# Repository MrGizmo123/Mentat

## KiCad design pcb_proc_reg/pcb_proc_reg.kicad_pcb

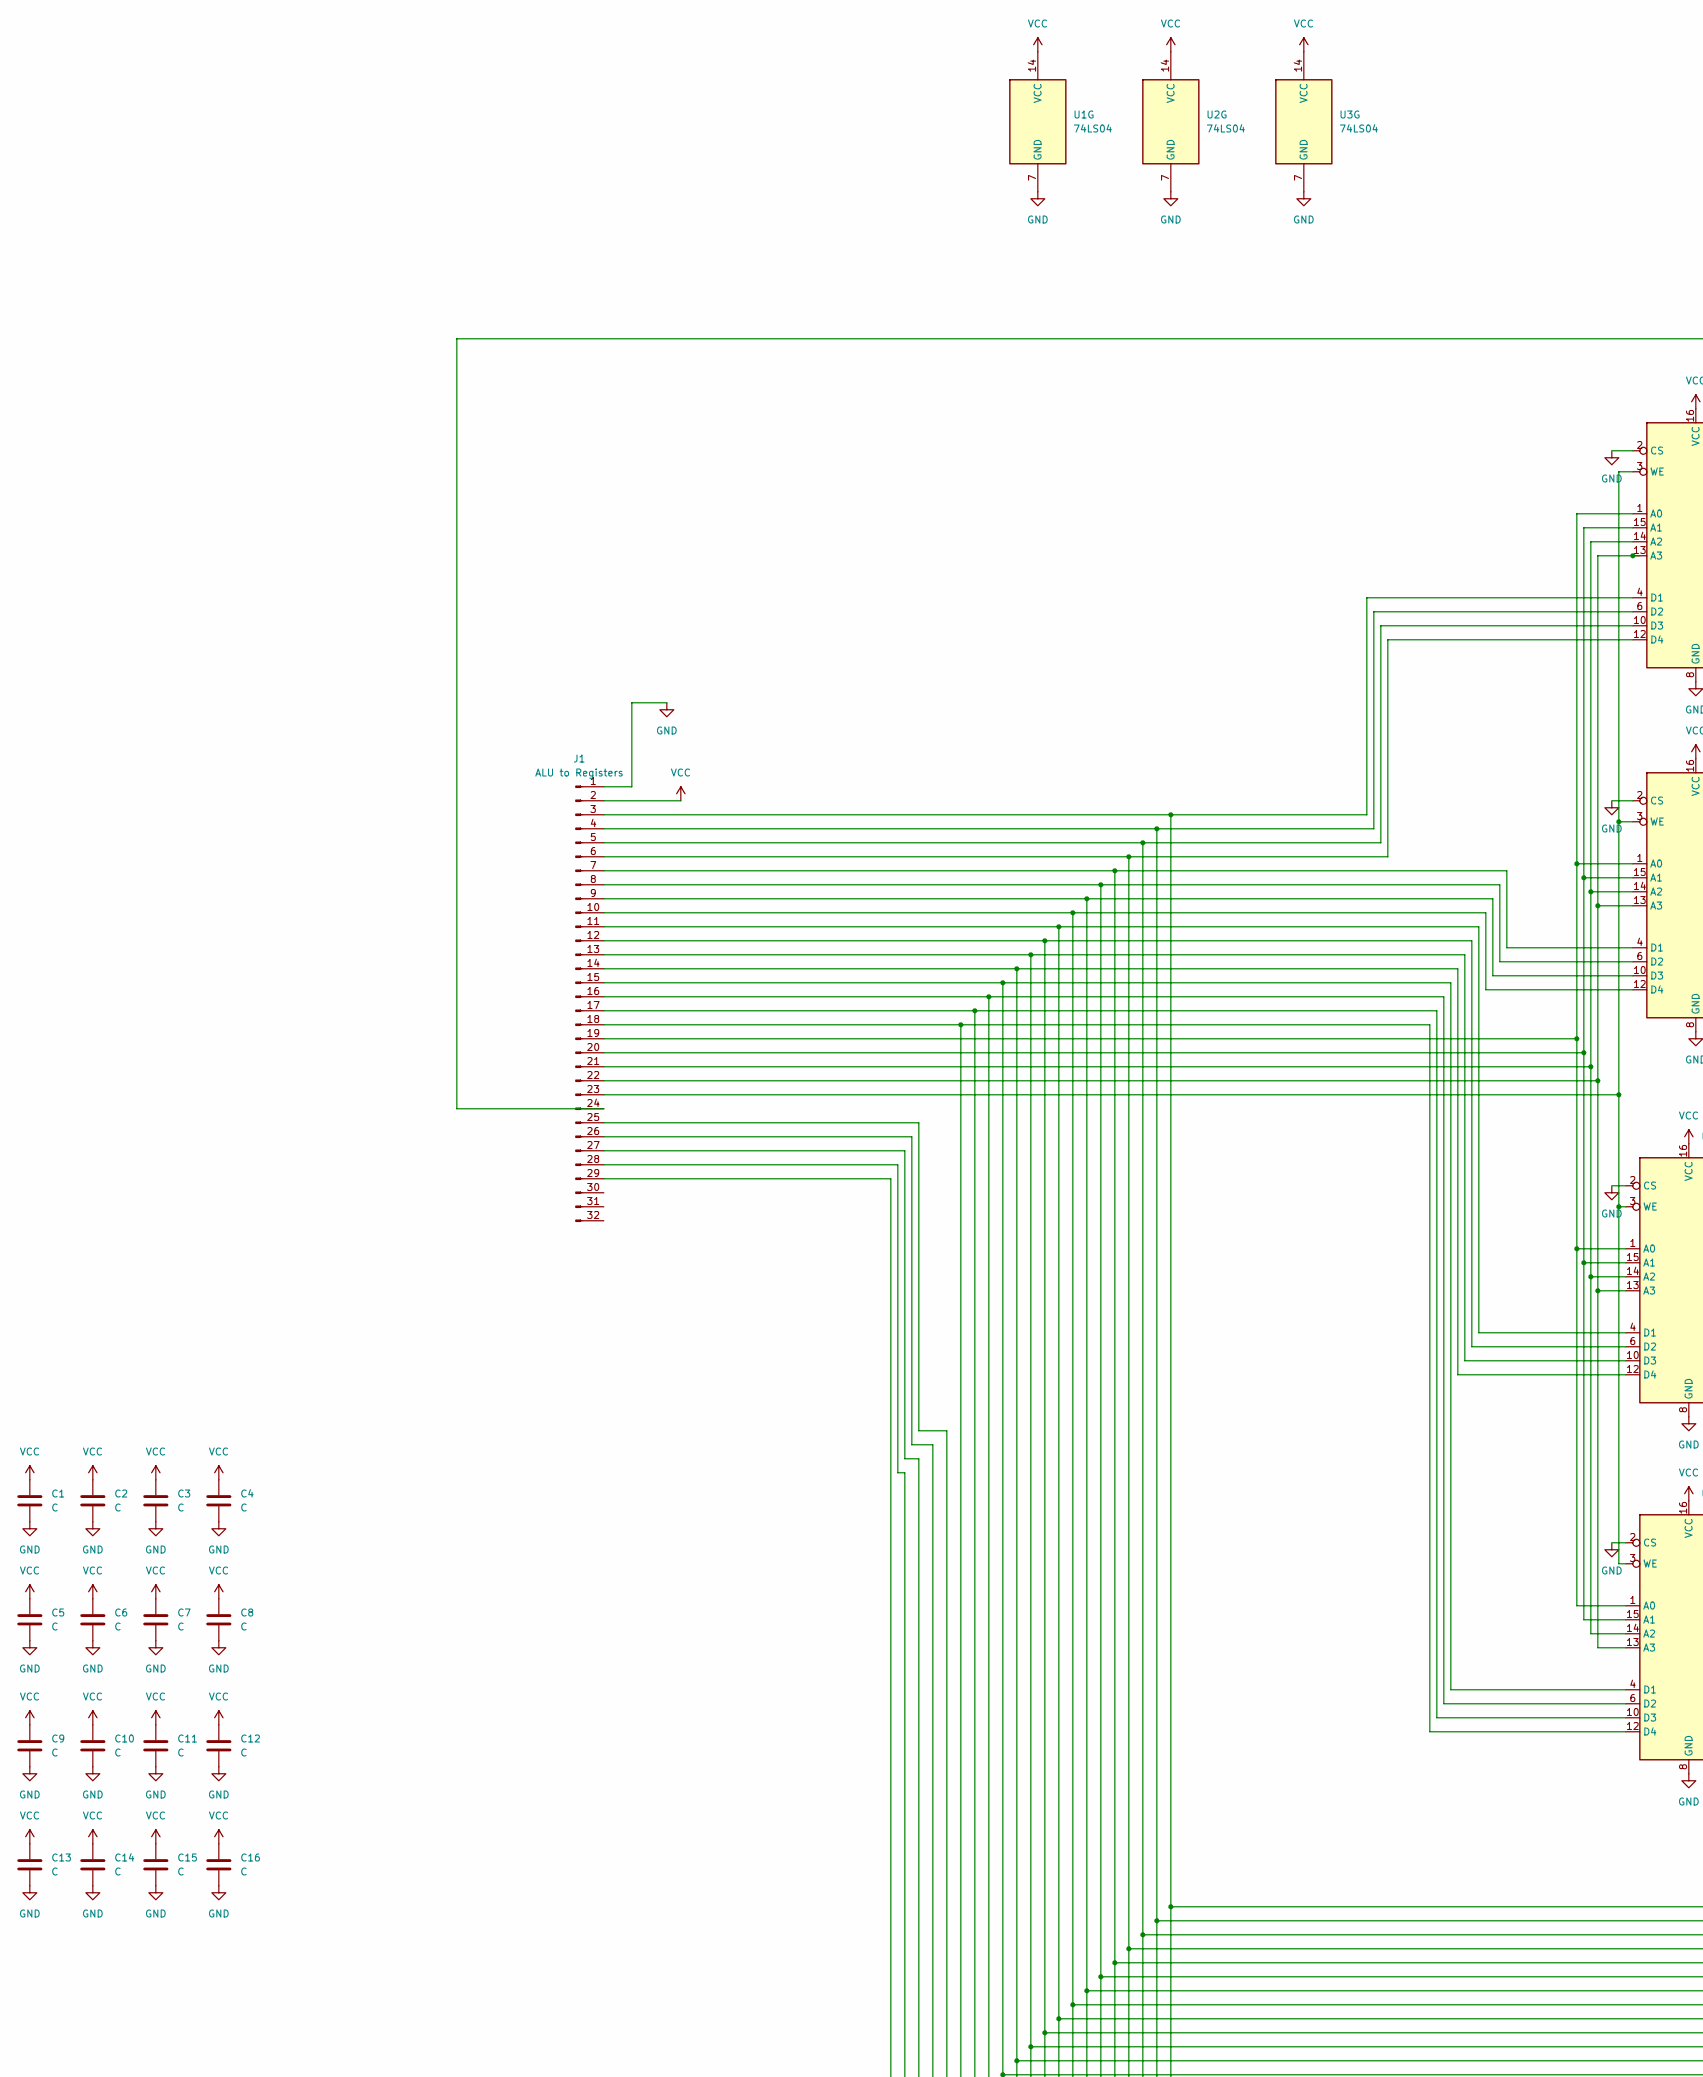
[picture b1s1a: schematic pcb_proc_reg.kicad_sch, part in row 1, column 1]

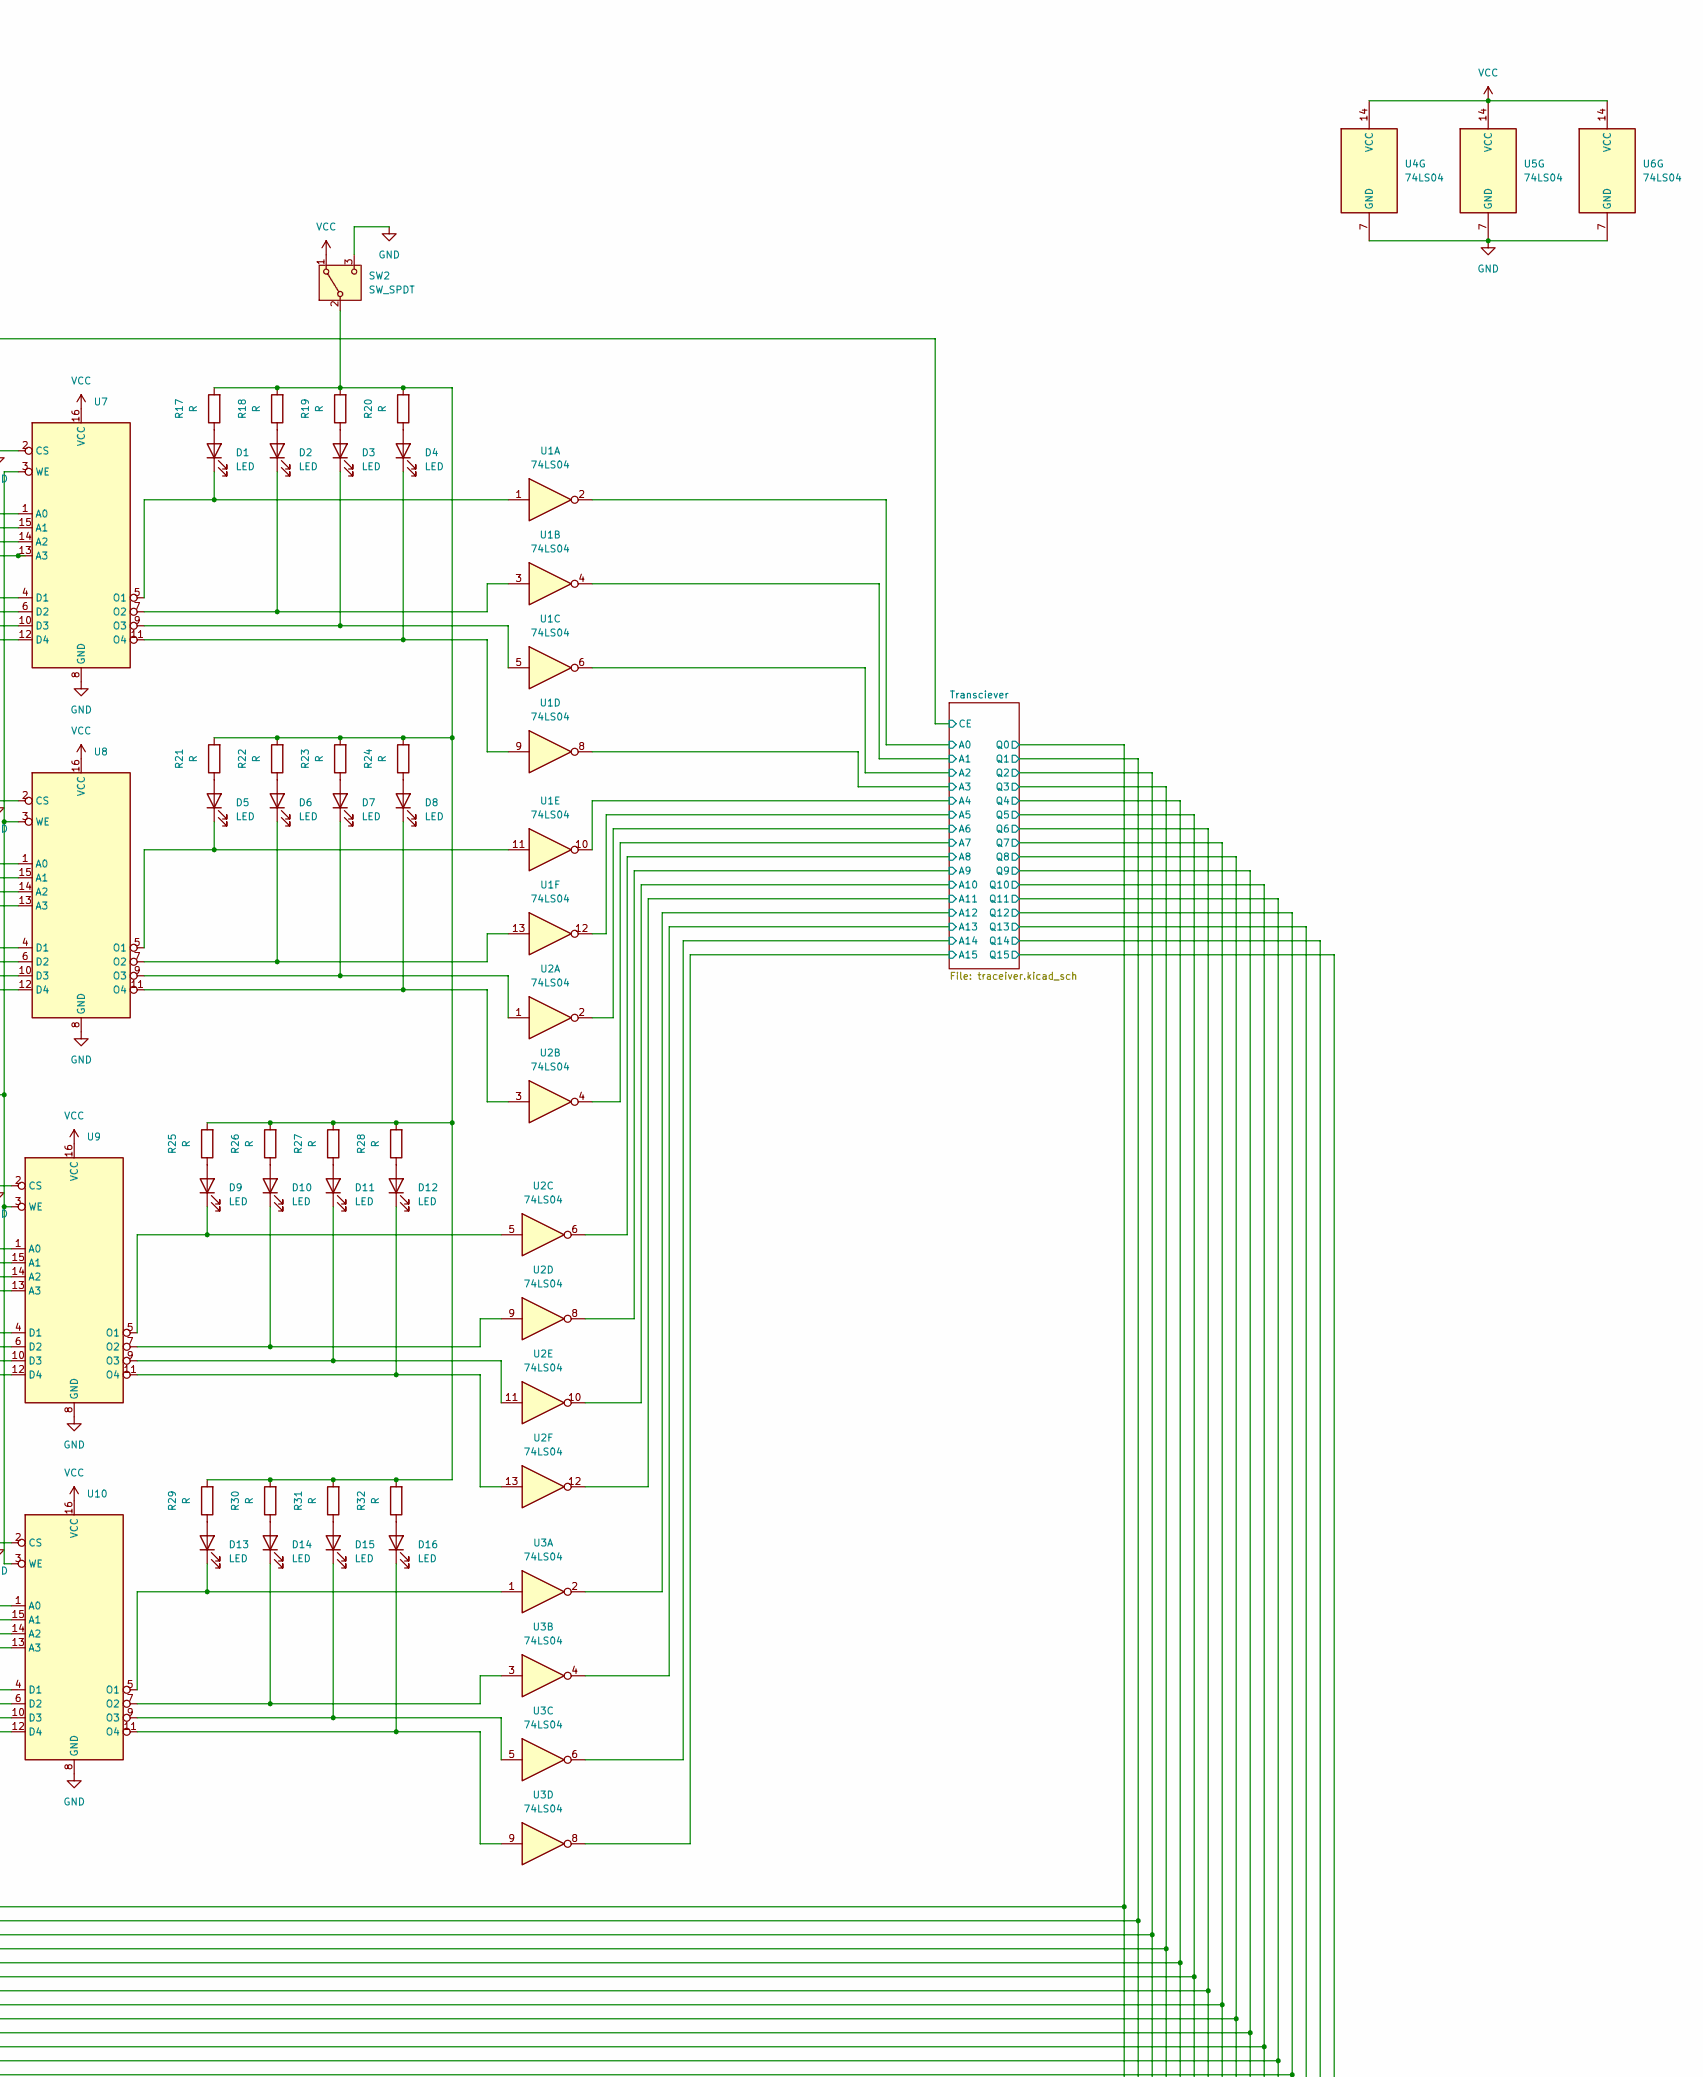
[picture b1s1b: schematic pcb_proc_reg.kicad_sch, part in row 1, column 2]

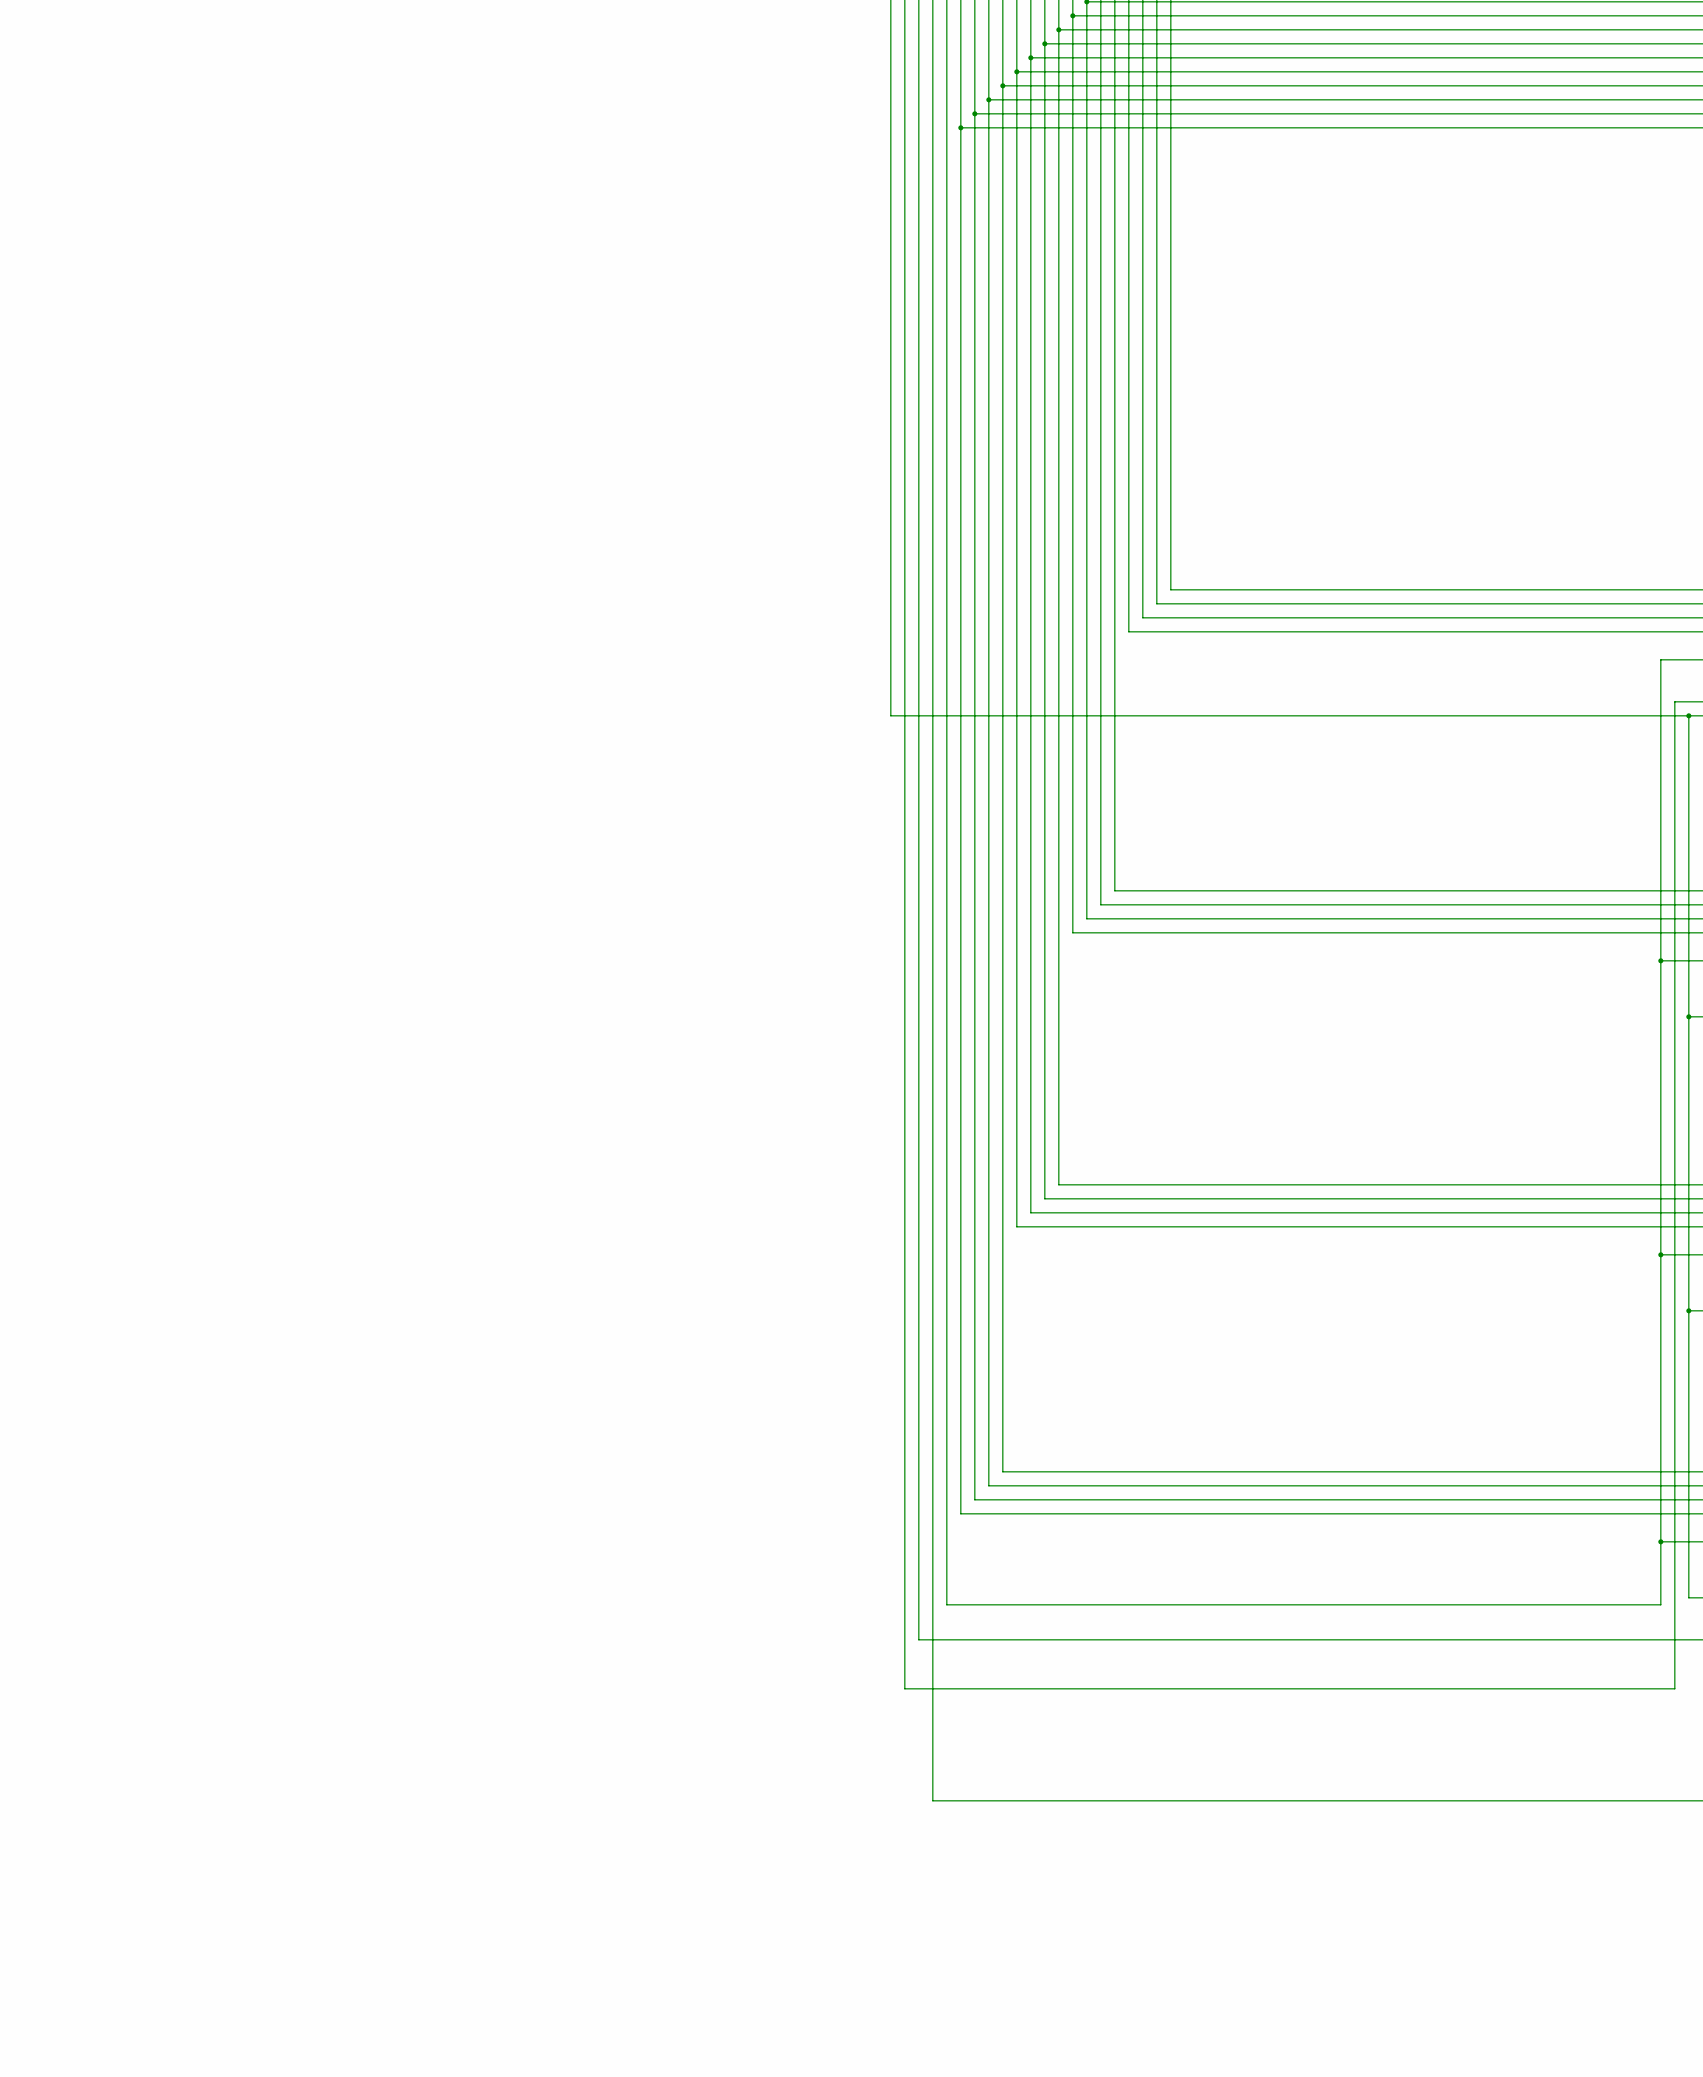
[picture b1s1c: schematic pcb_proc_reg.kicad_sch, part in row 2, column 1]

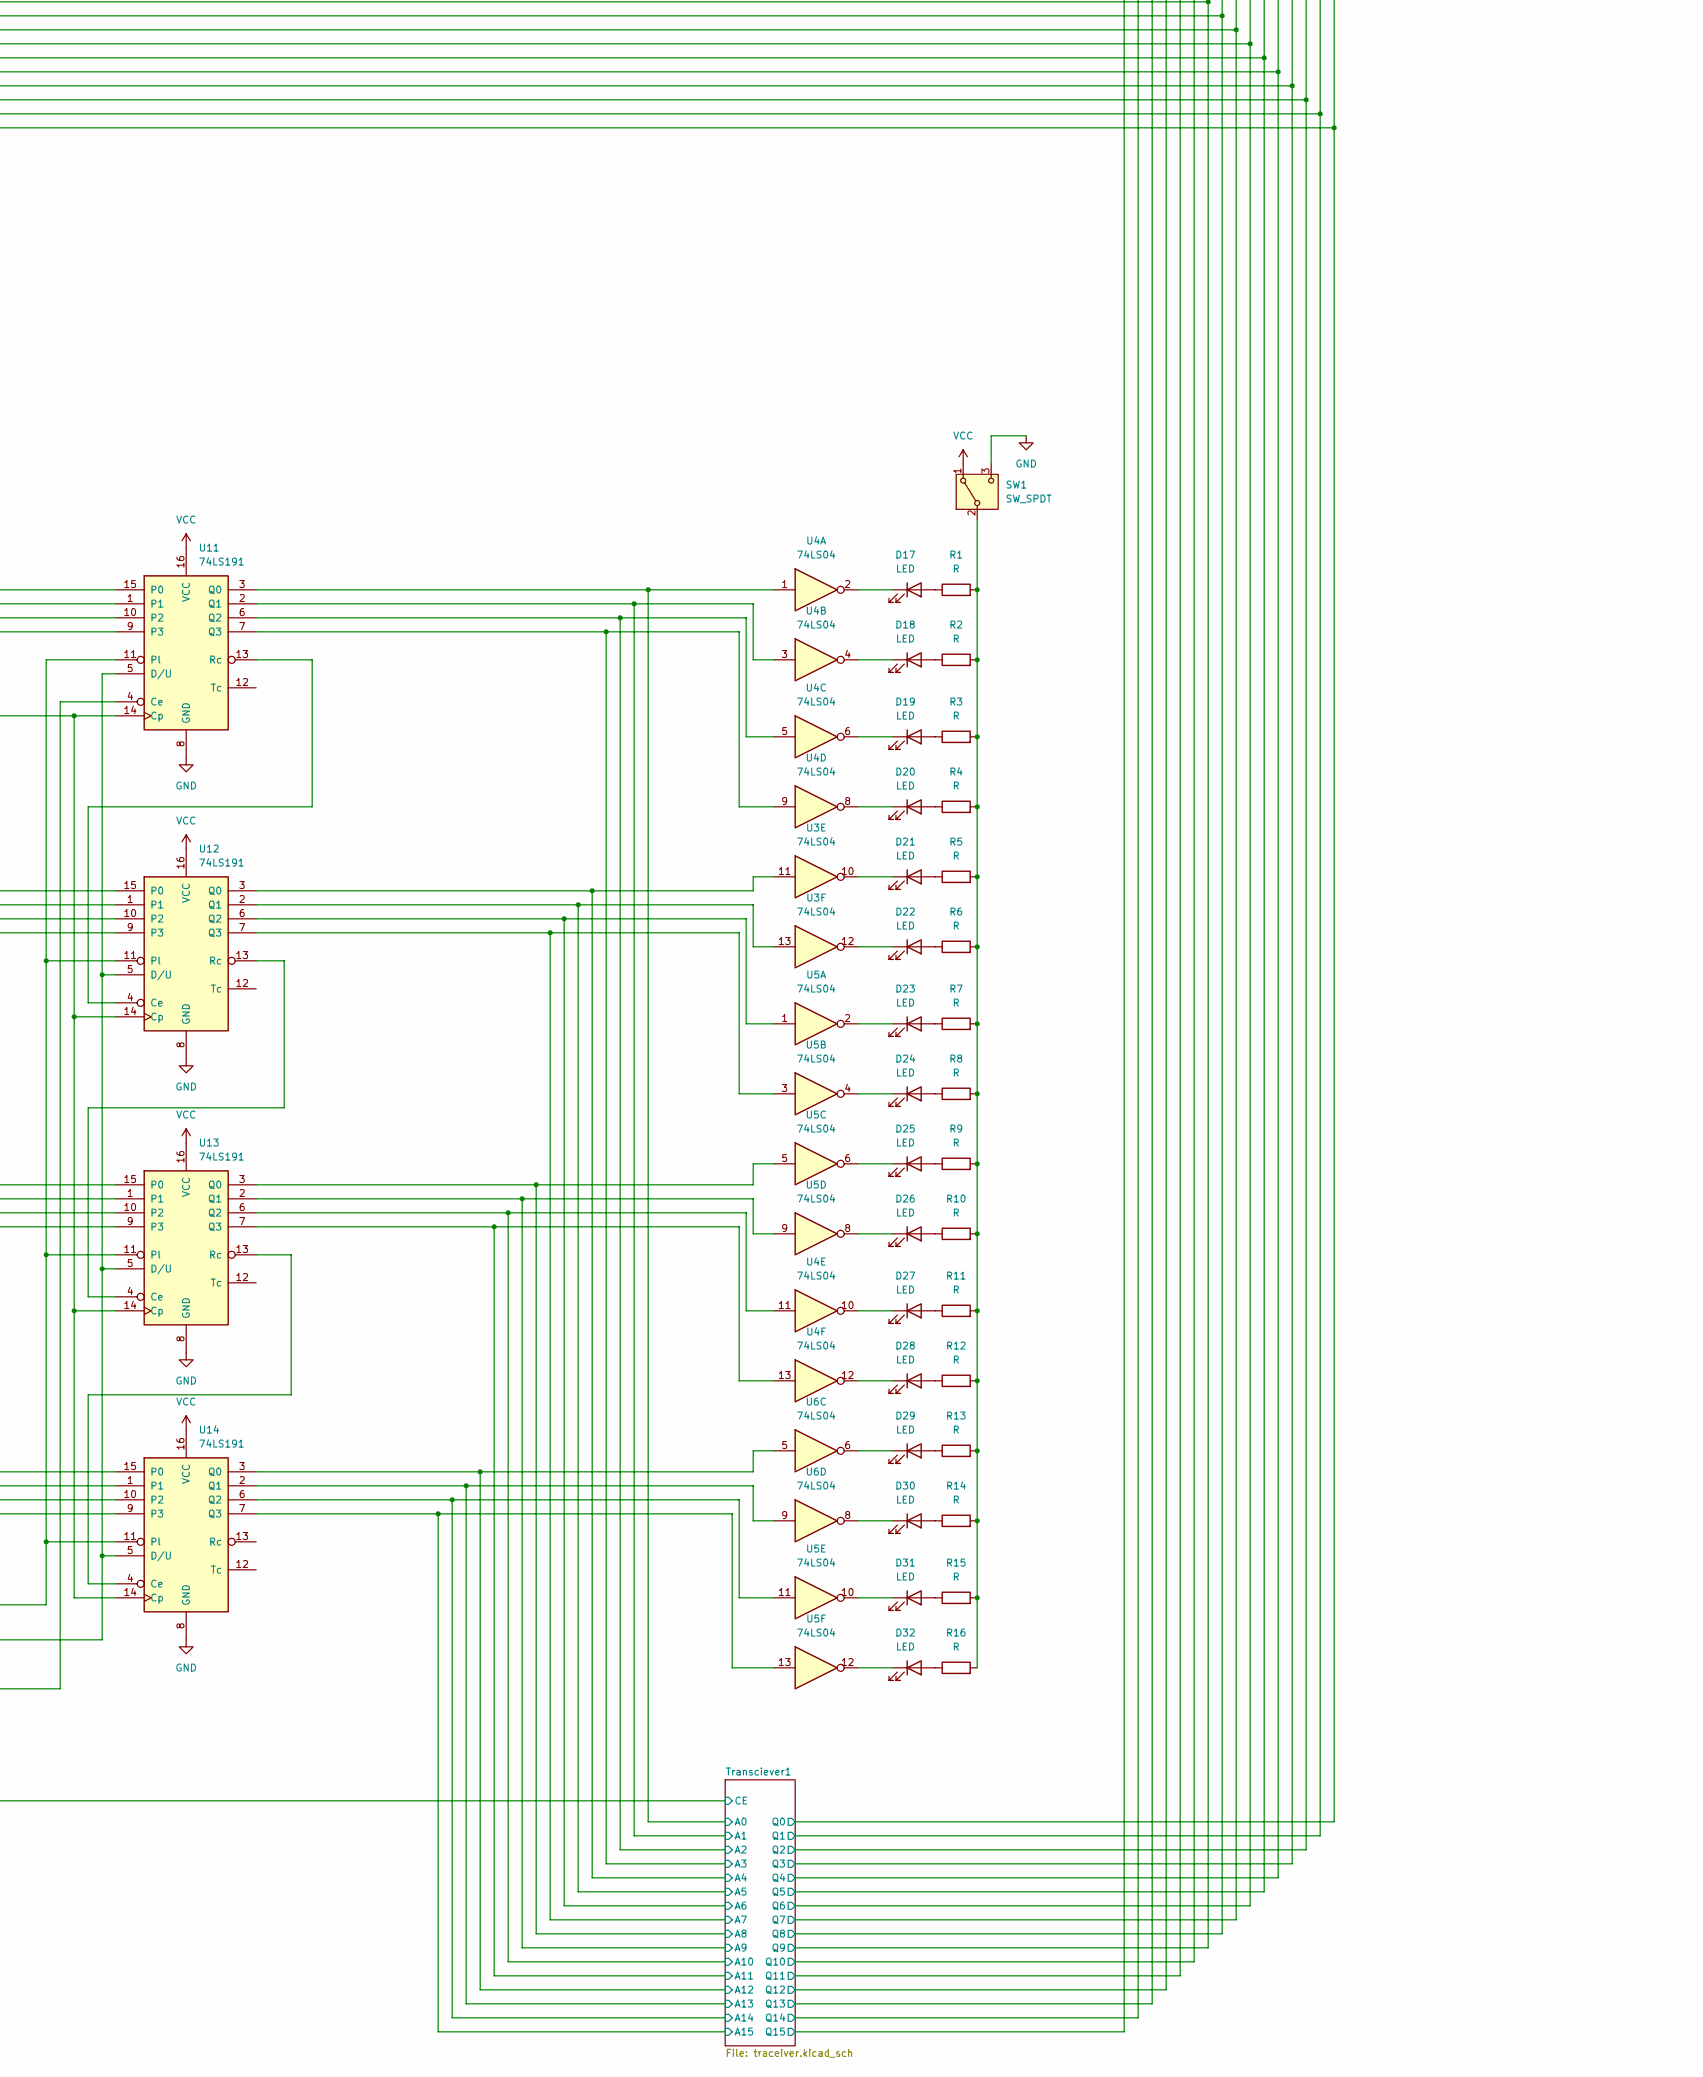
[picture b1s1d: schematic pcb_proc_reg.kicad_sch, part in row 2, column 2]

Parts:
C1, C2, C3, C4, C5, C6, C7, C8, C9, C10, C11, C12, C13, C14, C15, C16: C; C_0603_1608Metric
D1, D2, D3, D4, D5, D6, D7, D8, D9, D10, D11, D12, D13, D14, D15, D16, D17, D18, D19, D20, D21, D22, D23, D24, D25, D26, D27, D28, D29, D30, D31, D32: LED; LED_Rectangular_W5.0mm_H2.0mm
J1: ALU to Registers; PinHeader_2x16_P2.54mm_Vertical
R1, R2, R3, R4, R5, R6, R7, R8, R9, R10, R11, R12, R13, R14, R15, R16, R17, R18, R19, R20, R21, R22, R23, R24, R25, R26, R27, R28, R29, R30, R31, R32: R; R_0805_2012Metric
SW1, SW2: SW_SPDT; SW_E-Switch_EG1271_SPDT
U1, U2: 74LS04; DIP-14_W7.62mm_Socket_LongPads
U3, U4, U5, U6: 74LS04; DIP-14_W7.62mm_LongPads
U7, U8, U9, U10: DIP-16_W7.62mm_Socket_LongPads
U11, U12, U13, U14: 74LS191; DIP-16_W7.62mm_Socket_LongPads

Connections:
/Transciever1/A0: U4.1, U11.3 (Q0); also elsewhere on the board
/Transciever1/A1: U4.3, U11.2 (Q1); also elsewhere on the board
/Transciever1/A2: U4.5, U11.6 (Q2); also elsewhere on the board
/Transciever1/A3: U4.9, U11.7 (Q3); also elsewhere on the board
/Transciever1/A4: U3.11, U12.3 (Q0); also elsewhere on the board
/Transciever1/A5: U3.13, U12.2 (Q1); also elsewhere on the board
/Transciever1/A6: U5.1, U12.6 (Q2); also elsewhere on the board
/Transciever1/A7: U5.3, U12.7 (Q3); also elsewhere on the board
/Transciever1/A8: U5.5, U13.3 (Q0); also elsewhere on the board
/Transciever1/A9: U5.9, U13.2 (Q1); also elsewhere on the board
/Transciever1/A10: U4.11, U13.6 (Q2); also elsewhere on the board
/Transciever1/A11: U4.13, U13.7 (Q3); also elsewhere on the board
/Transciever1/A12: U6.5, U14.3 (Q0); also elsewhere on the board
/Transciever1/A13: U6.9, U14.2 (Q1); also elsewhere on the board
/Transciever1/A14: U5.11, U14.6 (Q2); also elsewhere on the board
/Transciever1/A15: U5.13, U14.7 (Q3); also elsewhere on the board
/Transciever1/CE: J1.26; also elsewhere on the board
/Transciever/A0: U1.2; also elsewhere on the board
/Transciever/A1: U1.4; also elsewhere on the board
/Transciever/A2: U1.6; also elsewhere on the board
/Transciever/A3: U1.8; also elsewhere on the board
/Transciever/A4: U1.10; also elsewhere on the board
/Transciever/A5: U1.12; also elsewhere on the board
/Transciever/A6: U2.2; also elsewhere on the board
/Transciever/A7: U2.4; also elsewhere on the board
/Transciever/A8: U2.6; also elsewhere on the board
/Transciever/A9: U2.8; also elsewhere on the board
/Transciever/A10: U2.10; also elsewhere on the board
/Transciever/A11: U2.12; also elsewhere on the board
/Transciever/A12: U3.2; also elsewhere on the board
/Transciever/A13: U3.4; also elsewhere on the board
/Transciever/A14: U3.6; also elsewhere on the board
/Transciever/A15: U3.8; also elsewhere on the board
/Transciever/CE: J1.24; also elsewhere on the board
/Transciever/Q0: J1.3, U7.4 (D1), U11.15 (P0); also elsewhere on the board
/Transciever/Q1: J1.4, U7.6 (D2), U11.1; also elsewhere on the board
/Transciever/Q2: J1.5, U7.10 (D3), U11.10 (P2); also elsewhere on the board
/Transciever/Q3: J1.6, U7.12 (D4), U11.9 (P3); also elsewhere on the board
/Transciever/Q4: J1.7, U8.4 (D1), U12.15 (P0); also elsewhere on the board
/Transciever/Q5: J1.8, U8.6 (D2), U12.1; also elsewhere on the board
/Transciever/Q6: J1.9, U8.10 (D3), U12.10 (P2); also elsewhere on the board
/Transciever/Q7: J1.10, U8.12 (D4), U12.9 (P3); also elsewhere on the board
/Transciever/Q8: J1.11, U9.4 (D1), U13.15 (P0); also elsewhere on the board
/Transciever/Q9: J1.12, U9.6 (D2), U13.1; also elsewhere on the board
/Transciever/Q10: J1.13, U9.10 (D3), U13.10 (P2); also elsewhere on the board
/Transciever/Q11: J1.14, U9.12 (D4), U13.9 (P3); also elsewhere on the board
/Transciever/Q12: J1.15, U10.4 (D1), U14.15 (P0); also elsewhere on the board
/Transciever/Q13: J1.16, U10.6 (D2), U14.1; also elsewhere on the board
/Transciever/Q14: J1.17, U10.10 (D3), U14.10 (P2); also elsewhere on the board
/Transciever/Q15: J1.18, U10.12 (D4), U14.9 (P3); also elsewhere on the board
GND: C1.2, C2.2, C3.2, C4.2, C5.2, C6.2, C7.2, C8.2, C9.2, C10.2, C11.2, C12.2, C13.2, C14.2, C15.2, C16.2, J1.1, SW1.3 (C), SW2.3 (C), U1.7 (GND), U2.7 (GND), U3.7 (GND), U4.7 (GND), U5.7 (GND), U6.7 (GND), U7.2 (CS), U7.8 (GND), U8.2 (CS), U8.8 (GND), U9.2 (CS), U9.8 (GND), U10.2 (CS), U10.8 (GND), U11.8 (GND), U12.8 (GND), U13.8 (GND), U14.8 (GND); also elsewhere on the board
unnamed: D1.2 (A), R17.1
unnamed: D1.1 (K), U1.1, U7.5 (O1)
unnamed: D2.2 (A), R18.1
unnamed: D2.1 (K), U1.3, U7.7 (O2)
unnamed: D3.2 (A), R19.1
unnamed: D3.1 (K), U1.5, U7.9 (O3)
unnamed: D4.2 (A), R20.1
unnamed: D4.1 (K), U1.9, U7.11 (O4)
unnamed: D5.2 (A), R21.1
unnamed: D5.1 (K), U1.11, U8.5 (O1)
unnamed: D6.2 (A), R22.1
unnamed: D6.1 (K), U1.13, U8.7 (O2)
unnamed: D7.2 (A), R23.1
unnamed: D7.1 (K), U2.1, U8.9 (O3)
unnamed: D8.2 (A), R24.1
unnamed: D8.1 (K), U2.3, U8.11 (O4)
unnamed: D9.2 (A), R25.1
unnamed: D9.1 (K), U2.5, U9.5 (O1)
unnamed: D10.2 (A), R26.1
unnamed: D10.1 (K), U2.9, U9.7 (O2)
unnamed: D11.2 (A), R27.1
unnamed: D11.1 (K), U2.11, U9.9 (O3)
unnamed: D12.2 (A), R28.1
unnamed: D12.1 (K), U2.13, U9.11 (O4)
unnamed: D13.2 (A), R29.1
unnamed: D13.1 (K), U3.1, U10.5 (O1)
unnamed: D14.2 (A), R30.1
unnamed: D14.1 (K), U3.3, U10.7 (O2)
unnamed: D15.2 (A), R31.1
unnamed: D15.1 (K), U3.5, U10.9 (O3)
unnamed: D16.2 (A), R32.1
unnamed: D16.1 (K), U3.9, U10.11 (O4)
unnamed: D17.2 (A), R1.1
unnamed: D17.1 (K), U4.2
unnamed: D18.2 (A), R2.1
unnamed: D18.1 (K), U4.4
unnamed: D19.2 (A), R3.1
unnamed: D19.1 (K), U4.6
unnamed: D20.2 (A), R4.1
unnamed: D20.1 (K), U4.8
unnamed: D21.2 (A), R5.1
unnamed: D21.1 (K), U3.10
unnamed: D22.2 (A), R6.1
unnamed: D22.1 (K), U3.12
unnamed: D23.2 (A), R7.1
unnamed: D23.1 (K), U5.2
unnamed: D24.2 (A), R8.1
unnamed: D24.1 (K), U5.4
unnamed: D25.2 (A), R9.1
unnamed: D25.1 (K), U5.6
unnamed: D26.2 (A), R10.1
unnamed: D26.1 (K), U5.8
unnamed: D27.2 (A), R11.1
unnamed: D27.1 (K), U4.10
unnamed: D28.2 (A), R12.1
unnamed: D28.1 (K), U4.12
unnamed: D29.2 (A), R13.1
unnamed: D29.1 (K), U6.6
unnamed: D30.2 (A), R14.1
unnamed: D30.1 (K), U6.8
unnamed: D31.2 (A), R15.1
unnamed: D31.1 (K), U5.10
unnamed: D32.2 (A), R16.1
unnamed: D32.1 (K), U5.12
unnamed: J1.19, U7.1 (A0), U8.1 (A0), U9.1 (A0), U10.1 (A0)
unnamed: J1.20, U7.15 (A1), U8.15 (A1), U9.15 (A1), U10.15 (A1)
unnamed: J1.21, U7.14 (A2), U8.14 (A2), U9.14 (A2), U10.14 (A2)
unnamed: J1.22, U7.13 (A3), U8.13 (A3), U9.13 (A3), U10.13 (A3)
unnamed: J1.23, U7.3 (WE), U8.3 (WE), U9.3 (WE), U10.3 (WE)
unnamed: J1.25, U11.11 (Pl), U12.11 (Pl), U13.11 (Pl), U14.11 (Pl)
unnamed: J1.27, U11.5 (D/U), U12.5 (D/U), U13.5 (D/U), U14.5 (D/U)
unnamed: J1.28, U11.4 (Ce)
unnamed: J1.29, U11.14 (Cp), U12.14 (Cp), U13.14 (Cp), U14.14 (Cp)
unnamed: R1.2, R2.2, R3.2, R4.2, R5.2, R6.2, R7.2, R8.2, R9.2, R10.2, R11.2, R12.2, R13.2, R14.2, R15.2, R16.2, SW1.2 (B)
unnamed: R17.2, R18.2, R19.2, R20.2, R21.2, R22.2, R23.2, R24.2, R25.2, R26.2, R27.2, R28.2, R29.2, R30.2, R31.2, R32.2, SW2.2 (B)
unnamed: U11.13 (Rc), U12.4 (Ce)
unnamed: U12.13 (Rc), U13.4 (Ce)
unnamed: U13.13 (Rc), U14.4 (Ce)
VCC: C1.1, C2.1, C3.1, C4.1, C5.1, C6.1, C7.1, C8.1, C9.1, C10.1, C11.1, C12.1, C13.1, C14.1, C15.1, C16.1, J1.2, SW1.1 (A), SW2.1 (A), U1.14 (VCC), U2.14 (VCC), U3.14 (VCC), U4.14 (VCC), U5.14 (VCC), U6.14 (VCC), U7.16 (VCC), U8.16 (VCC), U9.16 (VCC), U10.16 (VCC), U11.16 (VCC), U12.16 (VCC), U13.16 (VCC), U14.16 (VCC); also elsewhere on the board

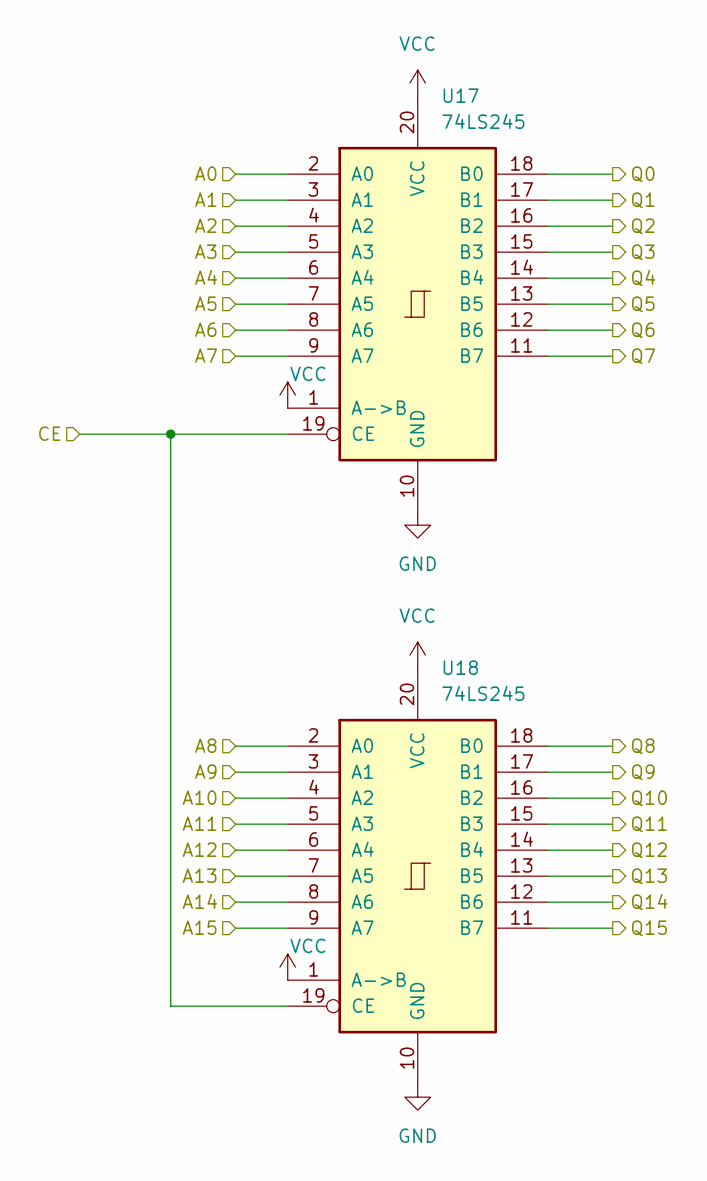
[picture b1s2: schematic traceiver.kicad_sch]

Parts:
U17, U18: 74LS245; DIP-20_W7.62mm_LongPads

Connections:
/Transciever1/A0: U17.2 (A0); also elsewhere on the board
/Transciever1/A1: U17.3 (A1); also elsewhere on the board
/Transciever1/A2: U17.4 (A2); also elsewhere on the board
/Transciever1/A3: U17.5 (A3); also elsewhere on the board
/Transciever1/A4: U17.6 (A4); also elsewhere on the board
/Transciever1/A5: U17.7 (A5); also elsewhere on the board
/Transciever1/A6: U17.8 (A6); also elsewhere on the board
/Transciever1/A7: U17.9 (A7); also elsewhere on the board
/Transciever1/A8: U18.2 (A0); also elsewhere on the board
/Transciever1/A9: U18.3 (A1); also elsewhere on the board
/Transciever1/A10: U18.4 (A2); also elsewhere on the board
/Transciever1/A11: U18.5 (A3); also elsewhere on the board
/Transciever1/A12: U18.6 (A4); also elsewhere on the board
/Transciever1/A13: U18.7 (A5); also elsewhere on the board
/Transciever1/A14: U18.8 (A6); also elsewhere on the board
/Transciever1/A15: U18.9 (A7); also elsewhere on the board
/Transciever1/CE: U17.19 (CE), U18.19 (CE); also elsewhere on the board
/Transciever/Q0: U18.11 (B7); also elsewhere on the board
/Transciever/Q1: U18.12 (B6); also elsewhere on the board
/Transciever/Q2: U18.13 (B5); also elsewhere on the board
/Transciever/Q3: U18.14 (B4); also elsewhere on the board
/Transciever/Q4: U18.15 (B3); also elsewhere on the board
/Transciever/Q5: U18.16 (B2); also elsewhere on the board
/Transciever/Q6: U18.17 (B1); also elsewhere on the board
/Transciever/Q7: U18.18 (B0); also elsewhere on the board
/Transciever/Q8: U17.11 (B7); also elsewhere on the board
/Transciever/Q9: U17.12 (B6); also elsewhere on the board
/Transciever/Q10: U17.13 (B5); also elsewhere on the board
/Transciever/Q11: U17.14 (B4); also elsewhere on the board
/Transciever/Q12: U17.15 (B3); also elsewhere on the board
/Transciever/Q13: U17.16 (B2); also elsewhere on the board
/Transciever/Q14: U17.17 (B1); also elsewhere on the board
/Transciever/Q15: U17.18 (B0); also elsewhere on the board
GND: U17.10 (GND), U18.10 (GND); also elsewhere on the board
VCC: U17.1 (A->B), U17.20 (VCC), U18.1 (A->B), U18.20 (VCC); also elsewhere on the board

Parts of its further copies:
U15, U16: 74LS245; DIP-20_W7.62mm_LongPads

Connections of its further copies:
/Transciever/A0: U15.2 (A0); also elsewhere on the board
/Transciever/A1: U15.3 (A1); also elsewhere on the board
/Transciever/A2: U15.4 (A2); also elsewhere on the board
/Transciever/A3: U15.5 (A3); also elsewhere on the board
/Transciever/A4: U15.6 (A4); also elsewhere on the board
/Transciever/A5: U15.7 (A5); also elsewhere on the board
/Transciever/A6: U15.8 (A6); also elsewhere on the board
/Transciever/A7: U15.9 (A7); also elsewhere on the board
/Transciever/A8: U16.2 (A0); also elsewhere on the board
/Transciever/A9: U16.3 (A1); also elsewhere on the board
/Transciever/A10: U16.4 (A2); also elsewhere on the board
/Transciever/A11: U16.5 (A3); also elsewhere on the board
/Transciever/A12: U16.6 (A4); also elsewhere on the board
/Transciever/A13: U16.7 (A5); also elsewhere on the board
/Transciever/A14: U16.8 (A6); also elsewhere on the board
/Transciever/A15: U16.9 (A7); also elsewhere on the board
/Transciever/CE: U15.19 (CE), U16.19 (CE); also elsewhere on the board
/Transciever/Q0: U15.18 (B0); also elsewhere on the board
/Transciever/Q1: U15.17 (B1); also elsewhere on the board
/Transciever/Q2: U15.16 (B2); also elsewhere on the board
/Transciever/Q3: U15.15 (B3); also elsewhere on the board
/Transciever/Q4: U15.14 (B4); also elsewhere on the board
/Transciever/Q5: U15.13 (B5); also elsewhere on the board
/Transciever/Q6: U15.12 (B6); also elsewhere on the board
/Transciever/Q7: U15.11 (B7); also elsewhere on the board
/Transciever/Q8: U16.18 (B0); also elsewhere on the board
/Transciever/Q9: U16.17 (B1); also elsewhere on the board
/Transciever/Q10: U16.16 (B2); also elsewhere on the board
/Transciever/Q11: U16.15 (B3); also elsewhere on the board
/Transciever/Q12: U16.14 (B4); also elsewhere on the board
/Transciever/Q13: U16.13 (B5); also elsewhere on the board
/Transciever/Q14: U16.12 (B6); also elsewhere on the board
/Transciever/Q15: U16.11 (B7); also elsewhere on the board
GND: U15.10 (GND), U16.10 (GND); also elsewhere on the board
VCC: U15.1 (A->B), U15.20 (VCC), U16.1 (A->B), U16.20 (VCC); also elsewhere on the board
